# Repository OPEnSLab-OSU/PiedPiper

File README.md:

# PiedPiper
Click [here](https://github.com/OPEnSLab-OSU/OPEnS-Lab-Home/wiki/Pied-Piper) for the full Pied Piper Wiki

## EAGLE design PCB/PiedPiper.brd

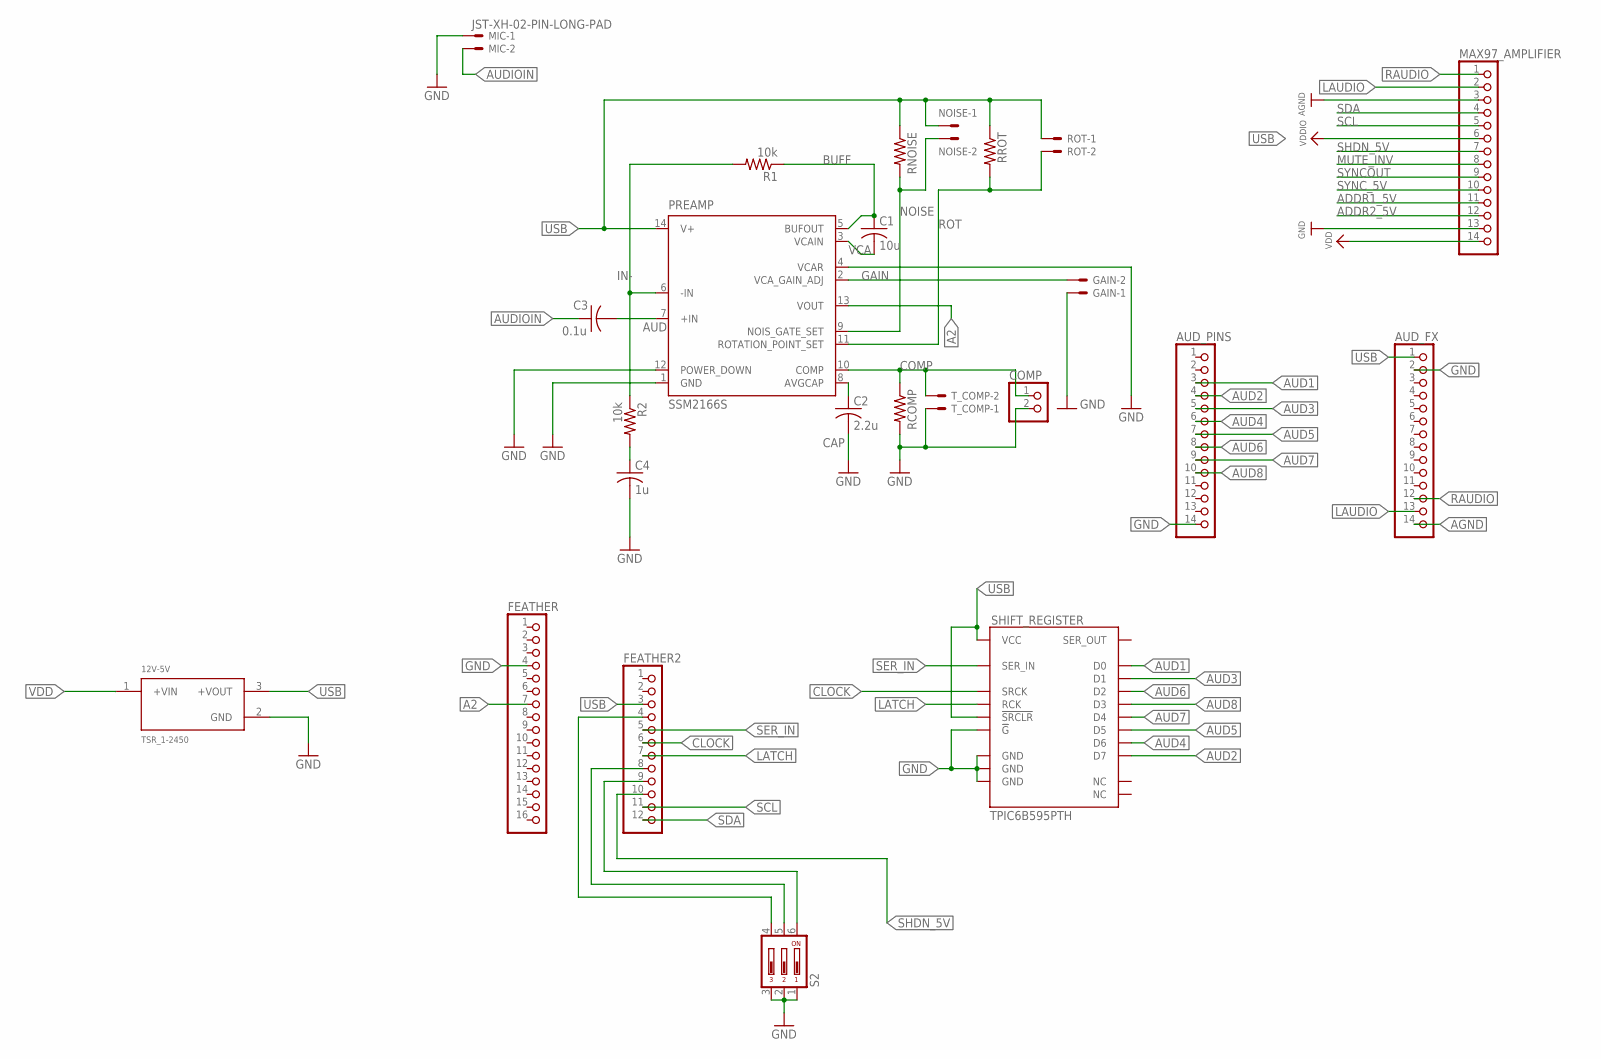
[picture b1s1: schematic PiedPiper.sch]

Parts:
12V-5V: TSR_1-2450; CONV_TSR_1-2450
AUD_FX: PINHD-1X14; 1X14
AUD_PINS: PINHD-1X14; 1X14
C1: 10u; C0805
C2: 2.2u; C0805
C3: 0.1u; C0805
C4: 1u; C0805
COMP: PINHD-1X2; 1X02
FEATHER: PINHD-1X16; 1X16
FEATHER2: PINHD-1X12; 1X12
GAIN: JST-XH-02-PIN-LONG-PAD; JST-XH-02-PACKAGE-LONG-PAD
MAX97_AMPLIFIER: HEADER-1X14; 1X14_ROUND70
MIC: JST-XH-02-PIN-LONG-PAD; JST-XH-02-PACKAGE-LONG-PAD
NOISE: JST-XH-02-PIN-LONG-PAD; JST-XH-02-PACKAGE-LONG-PAD
PREAMP: SSM2166S; SO14
R1, R2: 10k; R1206
RCOMP: R-US_R1206; R1206
RNOISE: R-US_R1206; R1206
ROT: JST-XH-02-PIN-LONG-PAD; JST-XH-02-PACKAGE-LONG-PAD
RROT: R-US_R1206; R1206
S2: DP03; DP-03
SHIFT_REGISTER: TPIC6B595PTH; DIL20
T_COMP: JST-XH-02-PIN-LONG-PAD; JST-XH-02-PACKAGE-LONG-PAD

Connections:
A2: FEATHER.7, PREAMP.13 (VOUT)
ADDR1_5V: MAX97_AMPLIFIER.11
ADDR2_5V: MAX97_AMPLIFIER.12
AGND: AUD_FX.14, MAX97_AMPLIFIER.3
AUD: C3.2, PREAMP.7 (+IN)
AUD1: AUD_PINS.3, SHIFT_REGISTER.4 (D0)
AUD2: AUD_PINS.4, SHIFT_REGISTER.17 (D7)
AUD3: AUD_PINS.5, SHIFT_REGISTER.5 (D1)
AUD4: AUD_PINS.6, SHIFT_REGISTER.16 (D6)
AUD5: AUD_PINS.7, SHIFT_REGISTER.15 (D5)
AUD6: AUD_PINS.8, SHIFT_REGISTER.6 (D2)
AUD7: AUD_PINS.9, SHIFT_REGISTER.14 (D4)
AUD8: AUD_PINS.10, SHIFT_REGISTER.7 (D3)
AUDIOIN: C3.1, MIC.2
BUFF: C1.1, PREAMP.5 (BUFOUT), R1.1
CAP: C2.1, PREAMP.8 (AVGCAP)
CLOCK: FEATHER2.6, SHIFT_REGISTER.13 (SRCK)
COMP: COMP.1, PREAMP.10 (COMP), RCOMP.1, T_COMP.2
GAIN: GAIN.2, PREAMP.2 (VCA_GAIN_ADJ)
GND: 12V-5V.2 (GND), AUD_FX.2, AUD_PINS.14, C2.2, C4.2, COMP.2, FEATHER.4, GAIN.1, MAX97_AMPLIFIER.13, MIC.1, PREAMP.1 (GND), PREAMP.4 (VCAR), PREAMP.12 (POWER_DOWN), RCOMP.2, S2.1, S2.2, S2.3, SHIFT_REGISTER.9 (!G), SHIFT_REGISTER.10 (GND), SHIFT_REGISTER.11 (GND), SHIFT_REGISTER.19 (GND), T_COMP.1
IN-: PREAMP.6 (-IN), R1.2, R2.1
LATCH: FEATHER2.7, SHIFT_REGISTER.12 (RCK)
LAUDIO: AUD_FX.13, MAX97_AMPLIFIER.2
MUTE_INV: MAX97_AMPLIFIER.8
unnamed: FEATHER2.8, S2.5
unnamed: FEATHER2.9, S2.6
unnamed: FEATHER2.4, S2.4
unnamed: C4.1, R2.2
NOISE: NOISE.2, PREAMP.9 (NOIS_GATE_SET), RNOISE.2
RAUDIO: AUD_FX.12, MAX97_AMPLIFIER.1
ROT: PREAMP.11 (ROTATION_POINT_SET), ROT.2, RROT.2
SCL: FEATHER2.11, MAX97_AMPLIFIER.5
SDA: FEATHER2.12, MAX97_AMPLIFIER.4
SER_IN: FEATHER2.5, SHIFT_REGISTER.3 (SER_IN)
SHDN_5V: FEATHER2.10, MAX97_AMPLIFIER.7
SYNCOUT: MAX97_AMPLIFIER.9
SYNC_5V: MAX97_AMPLIFIER.10
USB: 12V-5V.3 (+VOUT), AUD_FX.1, FEATHER2.3, MAX97_AMPLIFIER.6, NOISE.1, PREAMP.14 (V+), RNOISE.1, ROT.1, RROT.1, SHIFT_REGISTER.2 (VCC), SHIFT_REGISTER.8 (!SRCLR)
VCA: C1.2, PREAMP.3 (VCAIN)
VDD: 12V-5V.1 (+VIN), MAX97_AMPLIFIER.14

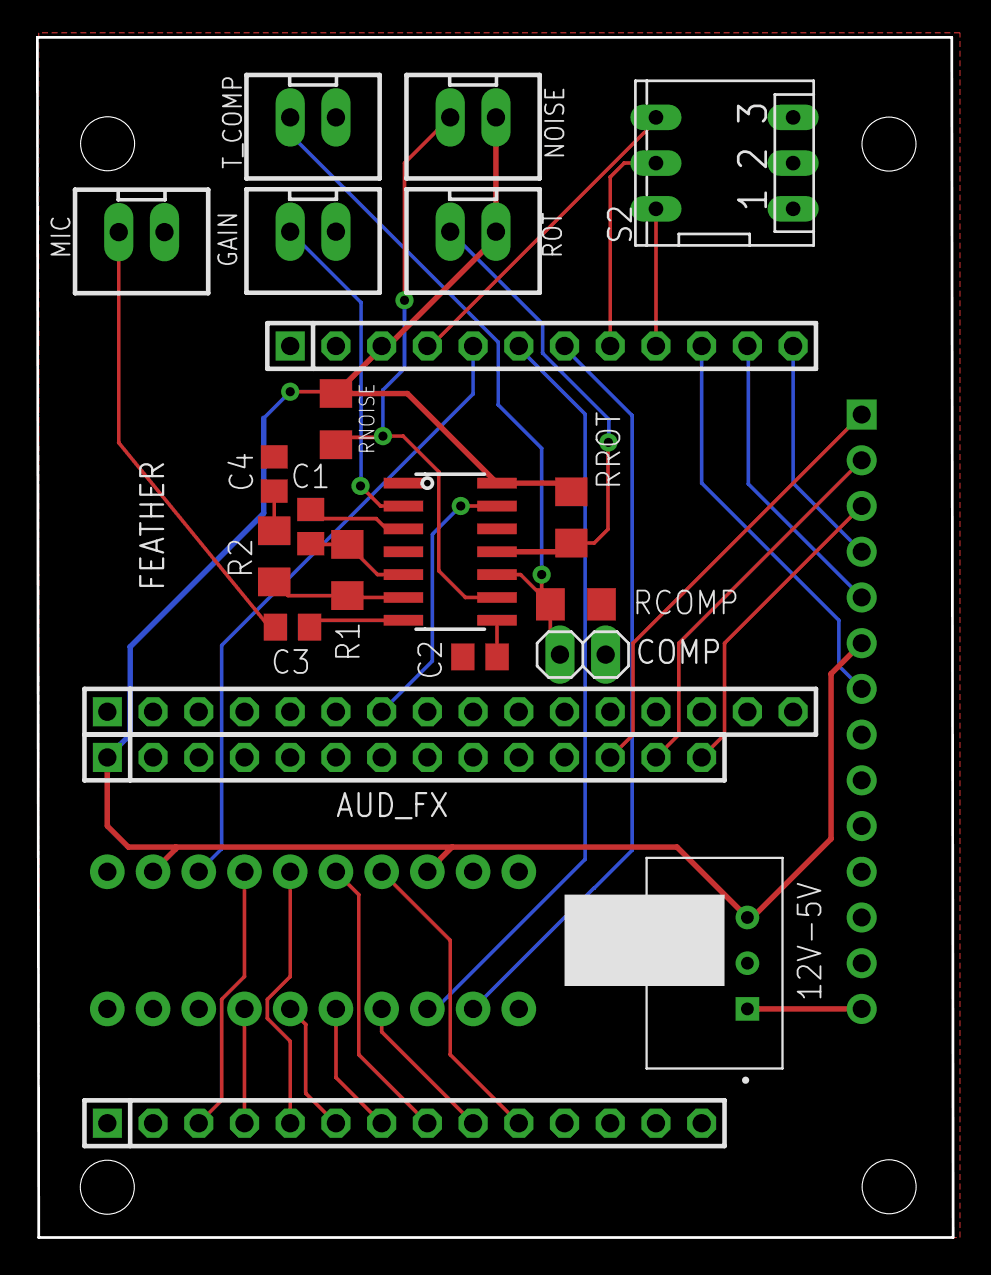
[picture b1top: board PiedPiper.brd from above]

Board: 2 copper layers, 50.9 x 66.7 mm, 24 parts (1 on the bottom side), 35 nets.

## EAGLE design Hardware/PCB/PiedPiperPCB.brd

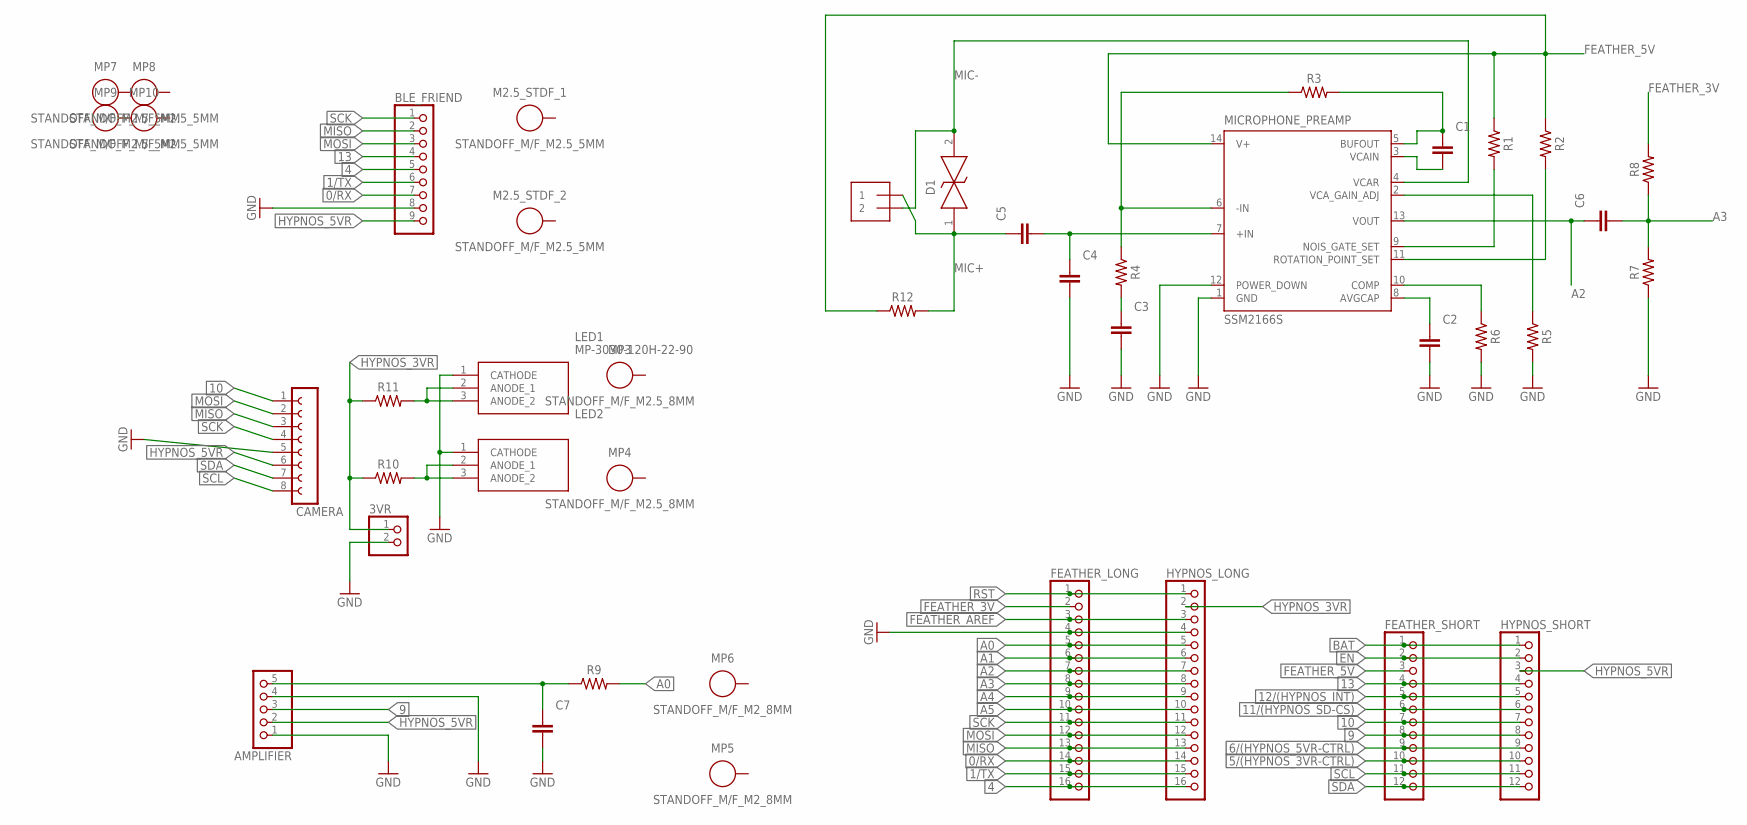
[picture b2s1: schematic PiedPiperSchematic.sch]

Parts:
3VR: PINHD-1X2; 1X02
AMPLIFIER: PINHD-1X05_2.54-S; 1X05-S
BLE_FRIEND: PINHD-1X09_2.54-S; 1X09-S
C1, C2, C3, C4, C5, C6, C7: C_CHIP-0805(2012-METRIC); CAPC2012X110
CAMERA: FE08W
D1: STS321033B100; SOD2613X100N
FEATHER_LONG: PINHD-1X16_2.54-S; 1X16-S
FEATHER_SHORT: PINHD-1X12_2.54-S; 1X12-S
HYPNOS_LONG: PINHD-1X16_2.54-S; 1X16-S
HYPNOS_SHORT: PINHD-1X12_2.54-S; 1X12-S
LED1, LED2: MP-3030-120H-22-90; MP3030120H2290
M2.5_STDF_1, M2.5_STDF_2: STANDOFF_M/F_M2.5_5MM; STANDOFF_HEX_MALE-FEMALE_500X500_M2.5X0.45_MTGP755H270
MICROPHONE_PREAMP: SSM2166S; SO14
MIC_INPT: 1X2-3.5MM
MP3, MP4: STANDOFF_M/F_M2.5_8MM; STANDOFF_HEX_MALE-FEMALE_500X800_M2.5X0.45_MTGP755H270
MP5, MP6: STANDOFF_M/F_M2_8MM; STANDOFF_HEX_MALE-FEMALE_400X800_M2X0.4_MTGP600H220
MP7, MP8, MP9, MP10: STANDOFF_M/F_M2.5_5MM; STANDOFF_HEX_MALE-FEMALE_500X500_M2.5X0.45_MTGP755H270
R1, R2, R3, R4, R5, R6, R7, R8, R9, R10, R11, R12: R-US_CHIP-1206(3216-METRIC); RESC3216X70

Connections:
0/RX: BLE_FRIEND.7, FEATHER_LONG.14, HYPNOS_LONG.14
1/TX: BLE_FRIEND.6, FEATHER_LONG.15, HYPNOS_LONG.15
4: BLE_FRIEND.5, FEATHER_LONG.16, HYPNOS_LONG.16
5/(HYPNOS_3VR-CTRL): FEATHER_SHORT.10, HYPNOS_SHORT.10
6/(HYPNOS_5VR-CTRL): FEATHER_SHORT.9, HYPNOS_SHORT.9
9: AMPLIFIER.3, FEATHER_SHORT.8, HYPNOS_SHORT.8
10: CAMERA.1, FEATHER_SHORT.7, HYPNOS_SHORT.7
11/(HYPNOS_SD-CS): FEATHER_SHORT.6, HYPNOS_SHORT.6
12/(HYPNOS_INT): FEATHER_SHORT.5, HYPNOS_SHORT.5
13: BLE_FRIEND.4, FEATHER_SHORT.4, HYPNOS_SHORT.4
A0: FEATHER_LONG.5, HYPNOS_LONG.5, R9.2
A1: FEATHER_LONG.6, HYPNOS_LONG.6
A2: C6.1, FEATHER_LONG.7, HYPNOS_LONG.7, MICROPHONE_PREAMP.13 (VOUT)
A3: C6.2, FEATHER_LONG.8, HYPNOS_LONG.8, R7.2, R8.1
A4: FEATHER_LONG.9, HYPNOS_LONG.9
A5: FEATHER_LONG.10, HYPNOS_LONG.10
AVGCAP: C2.1, MICROPHONE_PREAMP.8 (AVGCAP)
BAT: FEATHER_SHORT.1, HYPNOS_SHORT.1
BUFOUT: C1.1, MICROPHONE_PREAMP.5 (BUFOUT), R3.2
COMP: MICROPHONE_PREAMP.10 (COMP), R6.1
EN: FEATHER_SHORT.2, HYPNOS_SHORT.2
FEATHER_3V: FEATHER_LONG.2, R8.2
FEATHER_5V: FEATHER_SHORT.3, MICROPHONE_PREAMP.14 (V+), R1.1, R2.1, R12.1
FEATHER_AREF: FEATHER_LONG.3, HYPNOS_LONG.3
GND: 3VR.2, AMPLIFIER.1, AMPLIFIER.4, BLE_FRIEND.8, C2.2, C3.2, C4.2, C7.2, CAMERA.5, FEATHER_LONG.4, HYPNOS_LONG.4, LED1.1 (CATHODE), LED2.1 (CATHODE), MICROPHONE_PREAMP.1 (GND), MICROPHONE_PREAMP.12 (POWER_DOWN), R5.2, R6.2, R7.1
HYPNOS_3VR: 3VR.1, HYPNOS_LONG.2, R10.1, R11.1
HYPNOS_5VR: AMPLIFIER.2, BLE_FRIEND.9, CAMERA.6, HYPNOS_SHORT.3
IN+: C4.1, C5.2, MICROPHONE_PREAMP.7 (+IN)
IN-: MICROPHONE_PREAMP.6 (-IN), R3.1, R4.1
MIC+: C5.1, D1.1, MIC_INPT.1, R12.2
MIC-: D1.2, MICROPHONE_PREAMP.4 (VCAR), MIC_INPT.2
MISO: BLE_FRIEND.2, CAMERA.3, FEATHER_LONG.13, HYPNOS_LONG.13
MOSI: BLE_FRIEND.3, CAMERA.2, FEATHER_LONG.12, HYPNOS_LONG.12
unnamed: LED1.2 (ANODE_1), LED1.3 (ANODE_2), R11.2
unnamed: C3.1, R4.2
unnamed: AMPLIFIER.5, C7.1, R9.1
unnamed: LED2.2 (ANODE_1), LED2.3 (ANODE_2), R10.2
RGAIN: MICROPHONE_PREAMP.2 (VCA_GAIN_ADJ), R5.1
RNOISE: MICROPHONE_PREAMP.9 (NOIS_GATE_SET), R1.2
RROT: MICROPHONE_PREAMP.11 (ROTATION_POINT_SET), R2.2
RST: FEATHER_LONG.1, HYPNOS_LONG.1
SCK: BLE_FRIEND.1, CAMERA.4, FEATHER_LONG.11, HYPNOS_LONG.11
SCL: CAMERA.8, FEATHER_SHORT.11, HYPNOS_SHORT.11
SDA: CAMERA.7, FEATHER_SHORT.12, HYPNOS_SHORT.12
VCAIN: C1.2, MICROPHONE_PREAMP.3 (VCAIN)

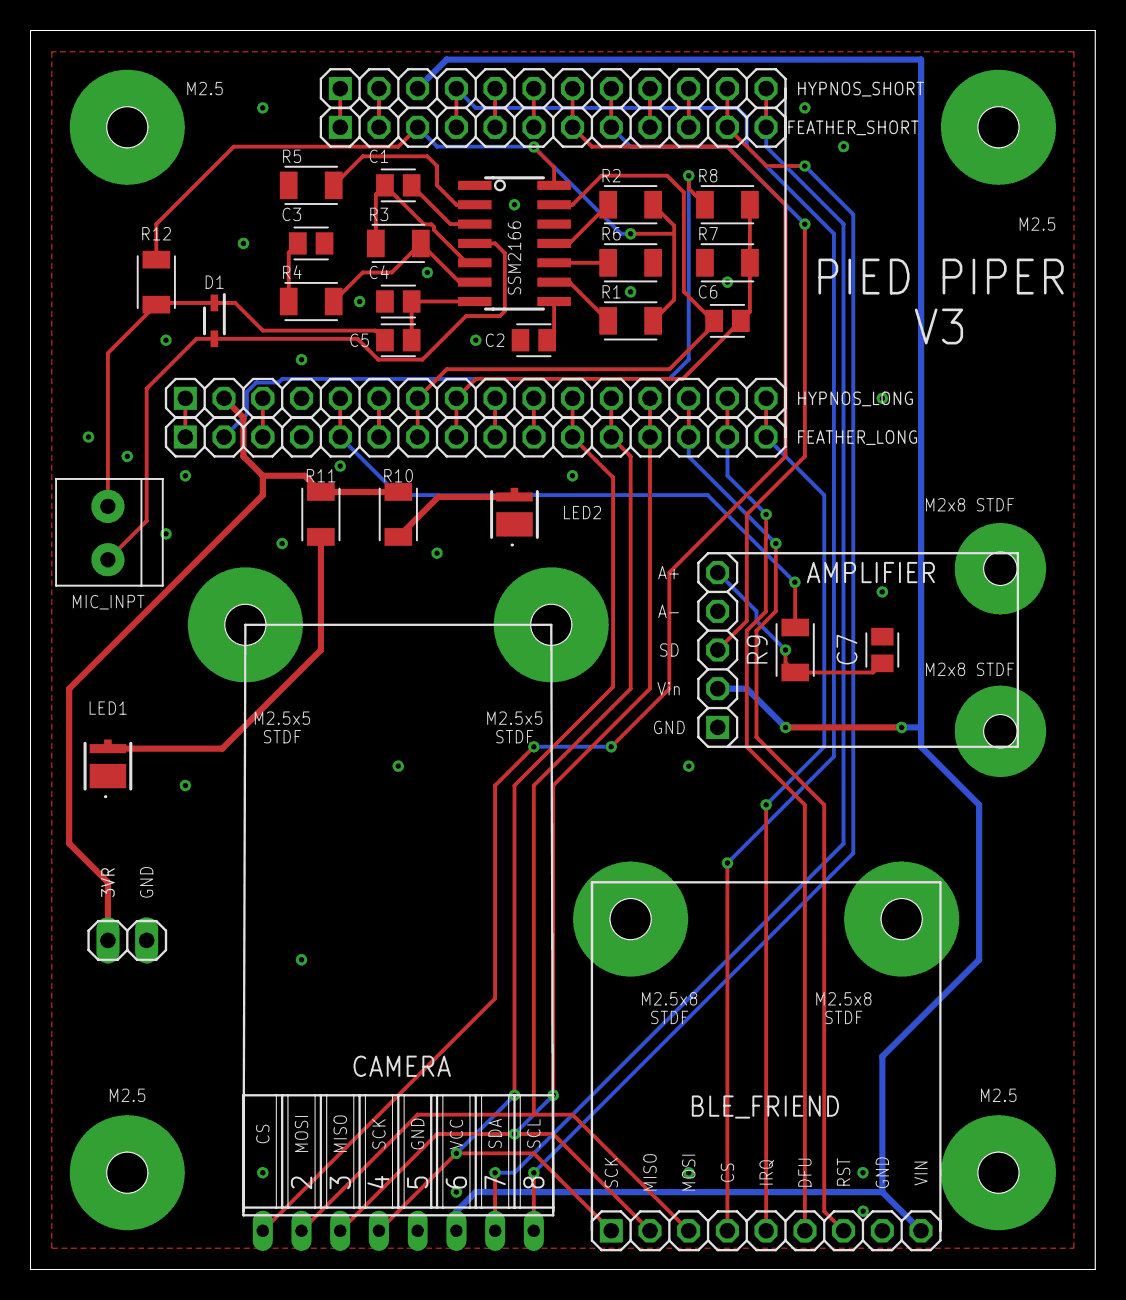
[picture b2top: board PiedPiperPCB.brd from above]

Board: 2 copper layers, 69.8 x 81.3 mm, 42 parts (0 on the bottom side), 45 nets.

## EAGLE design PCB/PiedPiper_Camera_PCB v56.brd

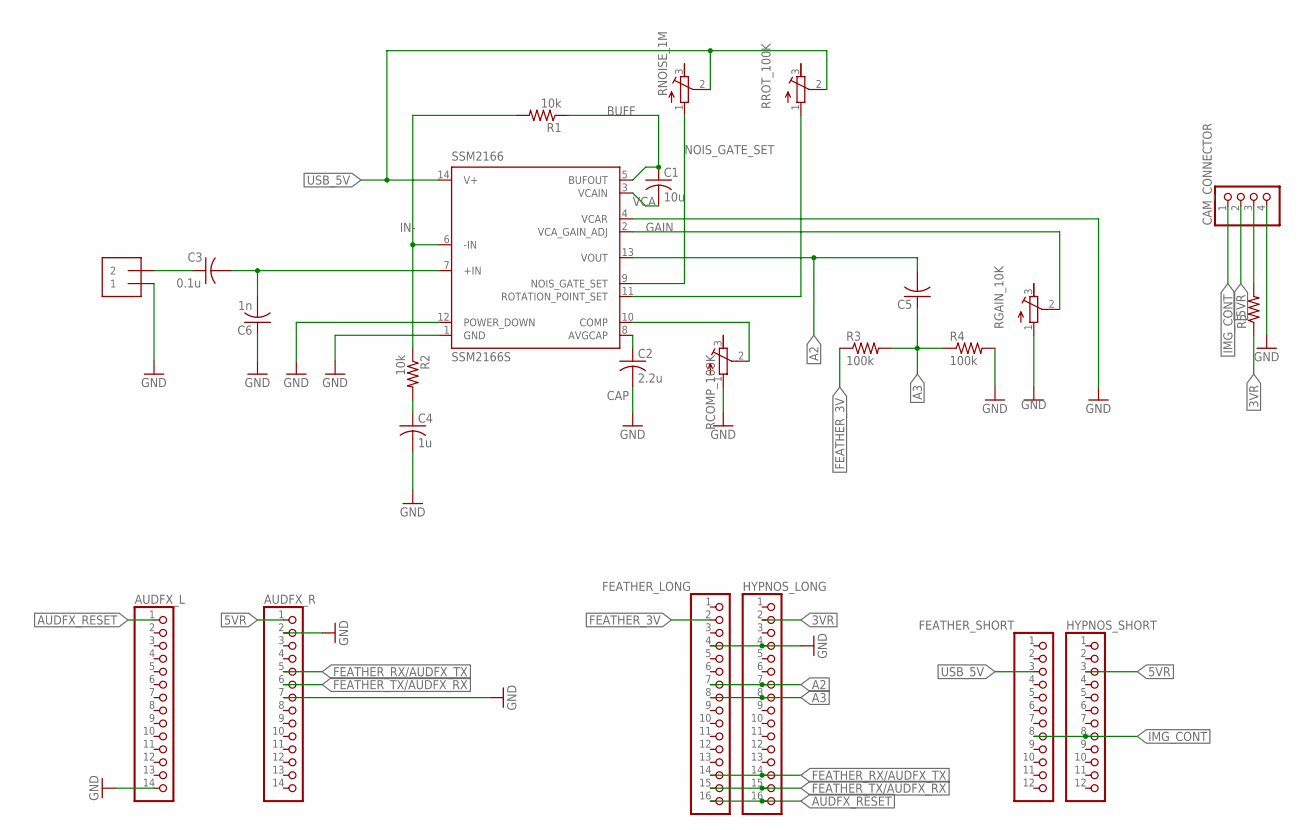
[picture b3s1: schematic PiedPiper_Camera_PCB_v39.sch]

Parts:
AUDFX_L: PINHD-1X14_2.54-S; 1X14-S
AUDFX_R: PINHD-1X14_2.54-S; 1X14-S
AUDIO_IN: 1X2-3.5MM
C1: 10u; C0805
C2: 2.2u; C0805
C3: 0.1u; C0805
C4: 1u; C0805
C5: C-USC0805; C0805
C6: 1n; C0805
CAM_CONNECTOR: PINHD-1X4; 1X04
FEATHER_LONG: PINHD-1X16_2.54-S; 1X16-S
FEATHER_SHORT: PINHD-1X12_2.54-S; 1X12-S
HYPNOS_LONG: PINHD-1X16_2.54-S; 1X16-S
HYPNOS_SHORT: PINHD-1X12_2.54-S; 1X12-S
R1, R2: 10k; R1206
R3, R4: 100k; R1206
R5: R-US_R1206; R1206
RCOMP_100K: R-TRIMM3296Y; RTRIM3296Y
RGAIN_10K: R-TRIMM3296Y; RTRIM3296Y
RNOISE_1M: R-TRIMM3296Y; RTRIM3296Y
RROT_100K: R-TRIMM3296Y; RTRIM3296Y
SSM2166: SSM2166S; SO14

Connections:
3VR: HYPNOS_LONG.2, R5.1
5VR: AUDFX_R.1, CAM_CONNECTOR.2, HYPNOS_SHORT.3
+IN: C3.2, C6.2, SSM2166.7 (+IN)
A2: C5.2, FEATHER_LONG.7, HYPNOS_LONG.7, SSM2166.13 (VOUT)
A3: C5.1, FEATHER_LONG.8, HYPNOS_LONG.8, R3.2, R4.1
AUDFX_RESET: AUDFX_L.1, FEATHER_LONG.16, HYPNOS_LONG.16
BUFF: C1.1, R1.1, SSM2166.5 (BUFOUT)
CAP: C2.1, SSM2166.8 (AVGCAP)
COMP: RCOMP_100K.2 (S), SSM2166.10 (COMP)
FEATHER_3V: FEATHER_LONG.2, R3.1
FEATHER_RX/AUDFX_TX: AUDFX_R.5, FEATHER_LONG.14, HYPNOS_LONG.14
FEATHER_TX/AUDFX_RX: AUDFX_R.6, FEATHER_LONG.15, HYPNOS_LONG.15
GAIN: RGAIN_10K.2 (S), SSM2166.2 (VCA_GAIN_ADJ)
GND: AUDFX_L.14, AUDFX_R.2, AUDFX_R.7, AUDIO_IN.1, C2.2, C4.2, C6.1, CAM_CONNECTOR.4, FEATHER_LONG.4, HYPNOS_LONG.4, R4.2, RCOMP_100K.1 (A), RGAIN_10K.1 (A), SSM2166.1 (GND), SSM2166.4 (VCAR), SSM2166.12 (POWER_DOWN)
IMG_CONT: CAM_CONNECTOR.1, FEATHER_SHORT.8, HYPNOS_SHORT.8
IN-: R1.2, R2.1, SSM2166.6 (-IN)
unnamed: CAM_CONNECTOR.3, R5.2
unnamed: AUDIO_IN.2, C3.1
unnamed: C4.1, R2.2
NOIS_GATE_SET: RNOISE_1M.1 (A), SSM2166.9 (NOIS_GATE_SET)
ROTATION_POINT_SET: RROT_100K.1 (A), SSM2166.11 (ROTATION_POINT_SET)
USB_5V: FEATHER_SHORT.3, RNOISE_1M.2 (S), RROT_100K.2 (S), SSM2166.14 (V+)
VCA: C1.2, SSM2166.3 (VCAIN)

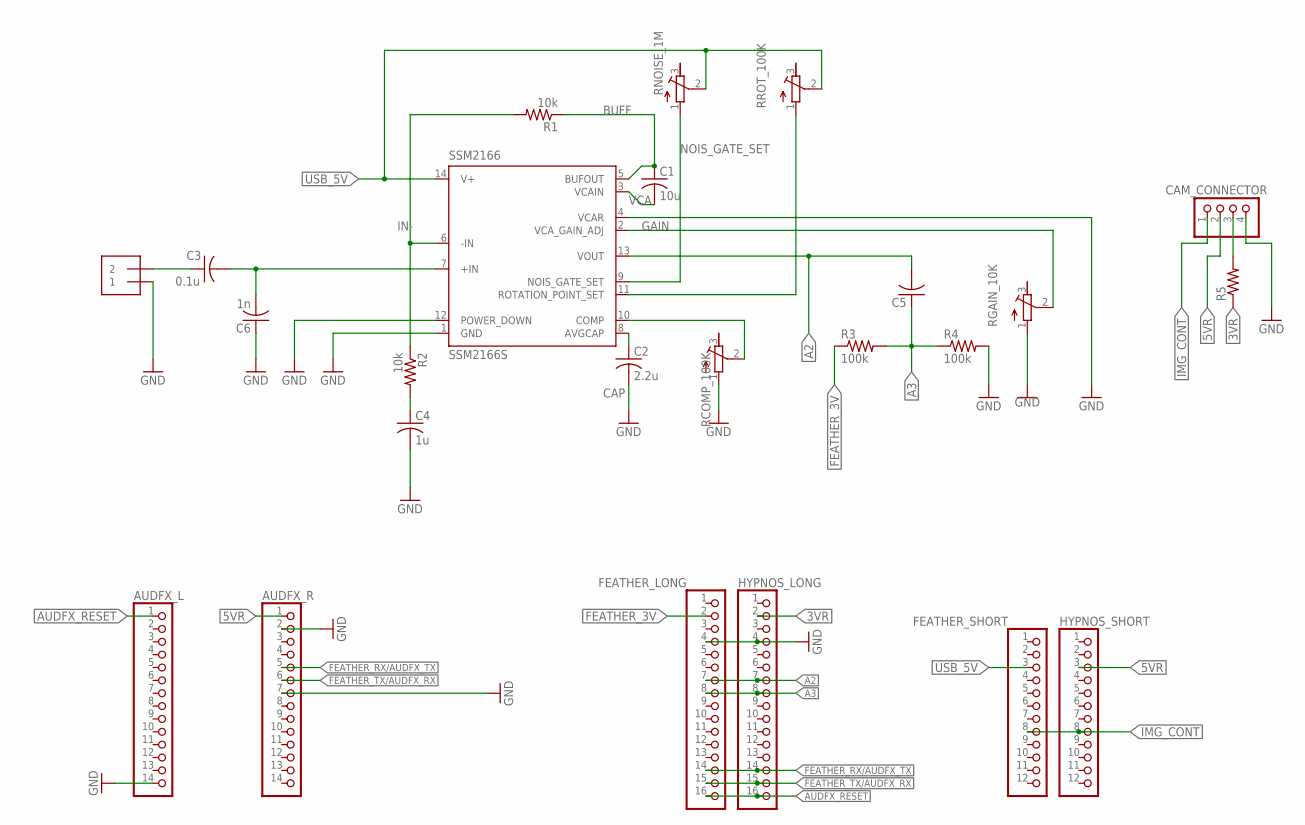
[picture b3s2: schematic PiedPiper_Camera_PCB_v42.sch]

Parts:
AUDFX_L: PINHD-1X14_2.54-S; 1X14-S
AUDFX_R: PINHD-1X14_2.54-S; 1X14-S
AUDIO_IN: 1X2-3.5MM
C1: 10u; C0805
C2: 2.2u; C0805
C3: 0.1u; C0805
C4: 1u; C0805
C5: C-USC0805; C0805
C6: 1n; C0805
CAM_CONNECTOR: PINHD-1X4; 1X04
FEATHER_LONG: PINHD-1X16_2.54-S; 1X16-S
FEATHER_SHORT: PINHD-1X12_2.54-S; 1X12-S
HYPNOS_LONG: PINHD-1X16_2.54-S; 1X16-S
HYPNOS_SHORT: PINHD-1X12_2.54-S; 1X12-S
R1, R2: 10k; R1206
R3, R4: 100k; R1206
R5: R-US_R1206; R1206
RCOMP_100K: R-TRIMM3296Y; RTRIM3296Y
RGAIN_10K: R-TRIMM3296Y; RTRIM3296Y
RNOISE_1M: R-TRIMM3296Y; RTRIM3296Y
RROT_100K: R-TRIMM3296Y; RTRIM3296Y
SSM2166: SSM2166S; SO14

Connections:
3VR: HYPNOS_LONG.2, R5.1
5VR: AUDFX_R.1, CAM_CONNECTOR.2, HYPNOS_SHORT.3
+IN: C3.2, C6.2, SSM2166.7 (+IN)
A2: C5.2, FEATHER_LONG.7, HYPNOS_LONG.7, SSM2166.13 (VOUT)
A3: C5.1, FEATHER_LONG.8, HYPNOS_LONG.8, R3.2, R4.1
AUDFX_RESET: AUDFX_L.1, FEATHER_LONG.16, HYPNOS_LONG.16
BUFF: C1.1, R1.1, SSM2166.5 (BUFOUT)
CAP: C2.1, SSM2166.8 (AVGCAP)
COMP: RCOMP_100K.2 (S), SSM2166.10 (COMP)
FEATHER_3V: FEATHER_LONG.2, R3.1
FEATHER_RX/AUDFX_TX: AUDFX_R.5, FEATHER_LONG.14, HYPNOS_LONG.14
FEATHER_TX/AUDFX_RX: AUDFX_R.6, FEATHER_LONG.15, HYPNOS_LONG.15
GAIN: RGAIN_10K.2 (S), SSM2166.2 (VCA_GAIN_ADJ)
GND: AUDFX_L.14, AUDFX_R.2, AUDFX_R.7, AUDIO_IN.1, C2.2, C4.2, C6.1, CAM_CONNECTOR.4, FEATHER_LONG.4, HYPNOS_LONG.4, R4.2, RCOMP_100K.1 (A), RGAIN_10K.1 (A), SSM2166.1 (GND), SSM2166.4 (VCAR), SSM2166.12 (POWER_DOWN)
IMG_CONT: CAM_CONNECTOR.1, FEATHER_SHORT.8, HYPNOS_SHORT.8
IN-: R1.2, R2.1, SSM2166.6 (-IN)
unnamed: CAM_CONNECTOR.3, R5.2
unnamed: AUDIO_IN.2, C3.1
unnamed: C4.1, R2.2
NOIS_GATE_SET: RNOISE_1M.1 (A), SSM2166.9 (NOIS_GATE_SET)
ROTATION_POINT_SET: RROT_100K.1 (A), SSM2166.11 (ROTATION_POINT_SET)
USB_5V: FEATHER_SHORT.3, RNOISE_1M.2 (S), RROT_100K.2 (S), SSM2166.14 (V+)
VCA: C1.2, SSM2166.3 (VCAIN)

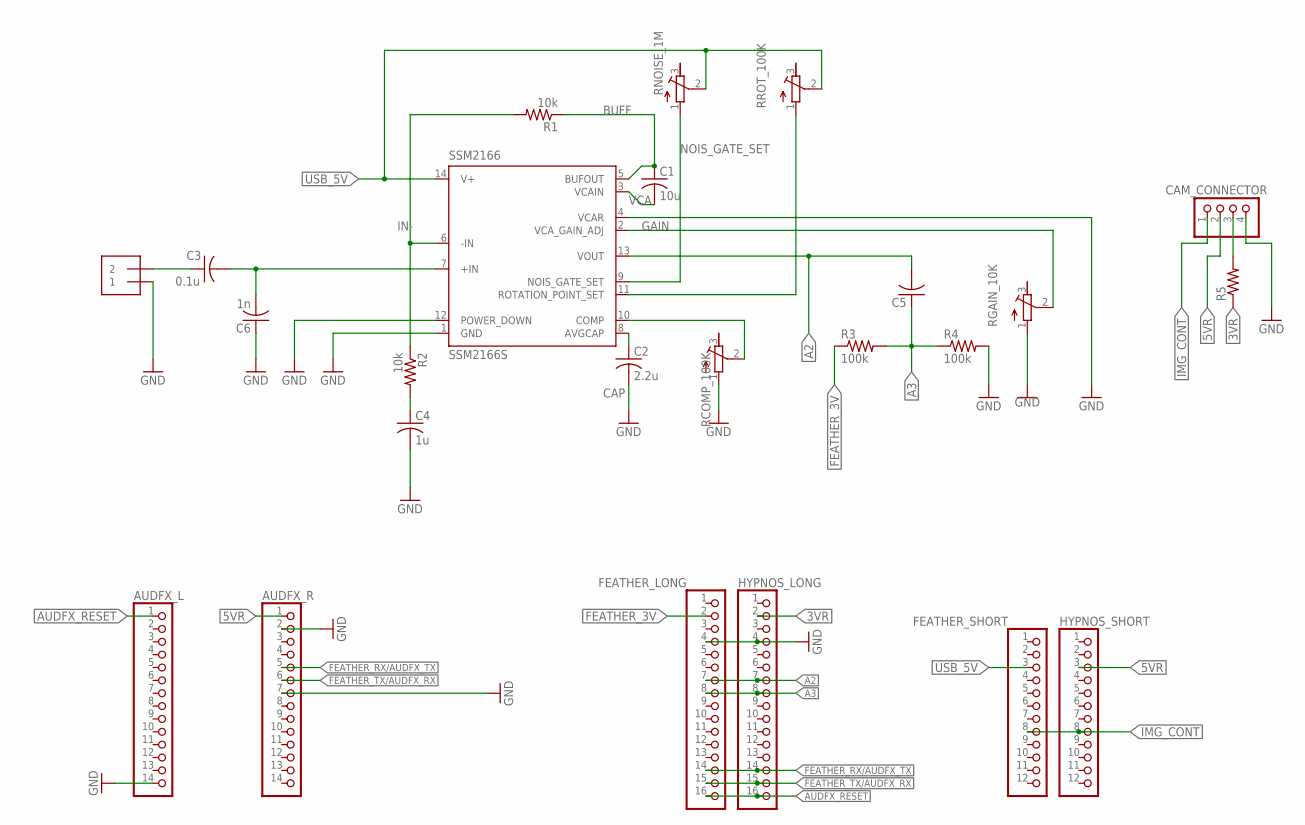
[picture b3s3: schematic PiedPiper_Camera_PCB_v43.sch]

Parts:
AUDFX_L: PINHD-1X14_2.54-S; 1X14-S
AUDFX_R: PINHD-1X14_2.54-S; 1X14-S
AUDIO_IN: 1X2-3.5MM
C1: 10u; C0805
C2: 2.2u; C0805
C3: 0.1u; C0805
C4: 1u; C0805
C5: C-USC0805; C0805
C6: 1n; C0805
CAM_CONNECTOR: PINHD-1X4; 1X04
FEATHER_LONG: PINHD-1X16_2.54-S; 1X16-S
FEATHER_SHORT: PINHD-1X12_2.54-S; 1X12-S
HYPNOS_LONG: PINHD-1X16_2.54-S; 1X16-S
HYPNOS_SHORT: PINHD-1X12_2.54-S; 1X12-S
R1, R2: 10k; R1206
R3, R4: 100k; R1206
R5: R-US_R1206; R1206
RCOMP_100K: R-TRIMM3296Y; RTRIM3296Y
RGAIN_10K: R-TRIMM3296Y; RTRIM3296Y
RNOISE_1M: R-TRIMM3296Y; RTRIM3296Y
RROT_100K: R-TRIMM3296Y; RTRIM3296Y
SSM2166: SSM2166S; SO14

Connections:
3VR: HYPNOS_LONG.2, R5.1
5VR: AUDFX_R.1, CAM_CONNECTOR.2, HYPNOS_SHORT.3
+IN: C3.2, C6.2, SSM2166.7 (+IN)
A2: C5.2, FEATHER_LONG.7, HYPNOS_LONG.7, SSM2166.13 (VOUT)
A3: C5.1, FEATHER_LONG.8, HYPNOS_LONG.8, R3.2, R4.1
AUDFX_RESET: AUDFX_L.1, FEATHER_LONG.16, HYPNOS_LONG.16
BUFF: C1.1, R1.1, SSM2166.5 (BUFOUT)
CAP: C2.1, SSM2166.8 (AVGCAP)
COMP: RCOMP_100K.2 (S), SSM2166.10 (COMP)
FEATHER_3V: FEATHER_LONG.2, R3.1
FEATHER_RX/AUDFX_TX: AUDFX_R.5, FEATHER_LONG.14, HYPNOS_LONG.14
FEATHER_TX/AUDFX_RX: AUDFX_R.6, FEATHER_LONG.15, HYPNOS_LONG.15
GAIN: RGAIN_10K.2 (S), SSM2166.2 (VCA_GAIN_ADJ)
GND: AUDFX_L.14, AUDFX_R.2, AUDFX_R.7, AUDIO_IN.1, C2.2, C4.2, C6.1, CAM_CONNECTOR.4, FEATHER_LONG.4, HYPNOS_LONG.4, R4.2, RCOMP_100K.1 (A), RGAIN_10K.1 (A), SSM2166.1 (GND), SSM2166.4 (VCAR), SSM2166.12 (POWER_DOWN)
IMG_CONT: CAM_CONNECTOR.1, FEATHER_SHORT.8, HYPNOS_SHORT.8
IN-: R1.2, R2.1, SSM2166.6 (-IN)
unnamed: CAM_CONNECTOR.3, R5.2
unnamed: AUDIO_IN.2, C3.1
unnamed: C4.1, R2.2
NOIS_GATE_SET: RNOISE_1M.1 (A), SSM2166.9 (NOIS_GATE_SET)
ROTATION_POINT_SET: RROT_100K.1 (A), SSM2166.11 (ROTATION_POINT_SET)
USB_5V: FEATHER_SHORT.3, RNOISE_1M.2 (S), RROT_100K.2 (S), SSM2166.14 (V+)
VCA: C1.2, SSM2166.3 (VCAIN)

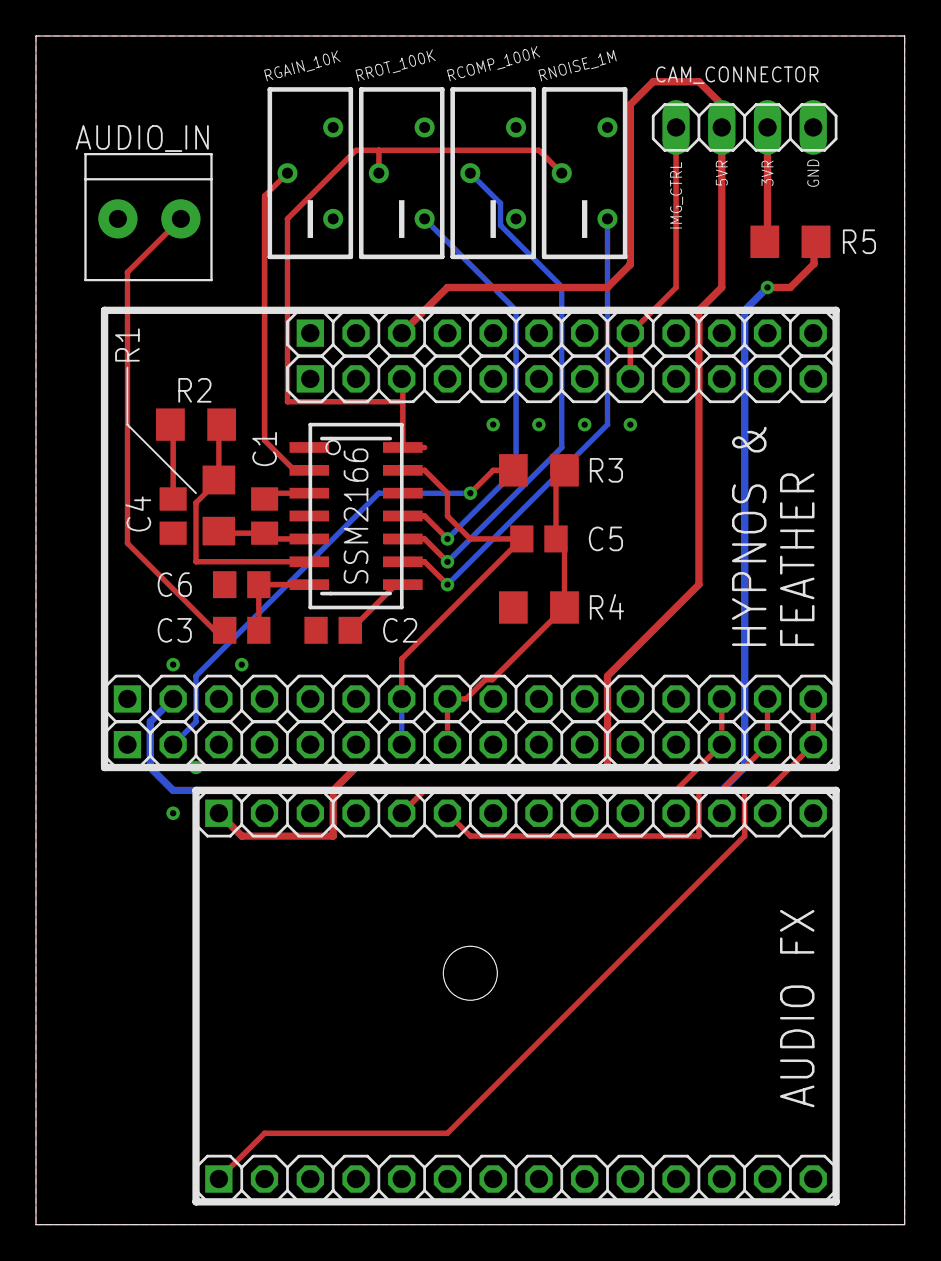
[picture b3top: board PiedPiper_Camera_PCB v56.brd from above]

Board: 2 copper layers, 48.3 x 66.0 mm, 24 parts (0 on the bottom side), 23 nets.

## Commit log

2019-11-12 Create foo
2019-11-12 Added Pied Piper 3D Models
2019-11-12 Added Pied Piper PCB Board
2019-11-12 Added Pied Piper Schematic
2019-11-22 Added Contact Mic 3D model
2019-11-22 Rename piedPiperMain.ino to Code/piedPiperMain.ino
2019-11-22 Updated playback
2020-01-27 Fixed a bug in detection algorithm
2020-04-30 Changed contact mic design
    New design gives the contact mic a stronger hold and uses less filament when printing
2020-06-15 Updated Pied Piper Trap STL files
2020-07-27 Added DEBUG mode
2020-07-27 Added hotswap DEBUG mode
2020-07-27 Fixed RTC/SD issue, added operation modes
    Adopted code to new PCB with shutdown for MAX9477 amplifier, added different operational modes(Full,No Playback, Gain Calibration, Audio Playback)
2020-08-25 Added 2 additional run modes
2020-08-28 Added function headers and improved comments
2020-09-14 Added code to parse recorded audio from Pied Piper
2020-09-14 Added automated grapher
    Generates waveforms of the data recorded from the piedPiper generated from the piedPiperAudioParser code
2020-09-14 updated code name
2020-10-19 Adjusting detection algorithm
2020-11-05 Added updated PCB
2020-11-09 Create STL
2020-11-10 Moved STL into folder
2021-01-21 Added noise generation software
2021-02-10 Added spectrogram tool
    Added a live spectrogram tool that can be used to stream processed audio off of the unit. A new operating mode was added (100) to use it.
2021-07-23 Camera
    Added software support for the camera
2021-07-23 Added camera support
    The camera used pin 10 for power control and pin 7 for imaging control
2021-08-06 Updated to reflect new hardware changes
    Camera power and imaging control pins have been remapped.
2021-08-09 Added status report log
    It's now easier to tell when problems occur (if any), because the system will periodically record whether or not it is alive, to the text file "Log.txt"
2021-08-15 Added serial debugging tools
2021-08-16 Reorganization
    Reorganized files and added .zenodo.json for publishing to Zenodo.
2021-08-16 Fixed json
    i missed a comma last time whoops
2021-08-18 Detection algorithm improved
    The detection algorithm is now less likely to output a false positive in response to intense transient noise.
2021-08-26 Updated PCB
2021-08-26 Added preview materials
    PDF and PNG files of the schematic and PCB have been added.
2021-08-26 Reorganized files
2021-08-26 Added CAM output zip
2021-08-27 Revised PCB
    Removed unnecessary ground traces, slightly reduced lengths of 5VR and 3VR traces, and added wire labels to camera connector pads.
2021-08-27 Another PCB revision
    Uploaded new PCB revision (in collaboration with Bryson) which includes ground plane vias to reduce capacitance.
2021-09-06 Added camera housing CAD files; fixed bug
2021-09-07 Fixed filenames
2021-09-07 Reorganized files and added sample printing utility
2021-09-07 Updated CAD files
2021-09-07 Adjusted detection algorithm frequency margin
2021-09-08 Fixed bug
    Added correct hypnos pin configuration to waveform viewer utility
2021-09-08 Added pre-arranged parts file for 3D printing.
2021-09-08 Added correct playback number for Hypnos
2021-09-09 SD always on
2021-09-11 Updated arranged parts file
2021-09-19 Fixed takePhoto
    Pin configuration commands were mistakenly commented out
2021-11-05 Uploaded parser to repo
    The parser used for generating spectrograms and audio files from raw detection data has been uploaded.
2021-11-05 Refactored code
2021-11-11 Improved code documentation
2021-12-27 Minor refactoring
2022-05-09 Fixed typo
2022-05-09 Removed files that were deleted from camera branch
2022-05-09 Added new PCB files
2022-05-09 Added labels to 3VR pads
2022-05-09 Fixed schematic and PCB version issue
2022-05-12 Updated CAM files
2022-06-15 Added support for new playback hardware
2022-07-18 Updated detection algorithm parameters
2023-02-02 Reformatting & documentation
2023-06-27 Added ArduinoFFTFloat dependency
2023-07-07 Reorganized files & added some utilities
2023-08-28 adding dependencies folder along with minor changes to software
2023-09-19 downsampling implementation v1
2023-10-07 resampling implemented
2023-10-10 resampling fixes
2023-10-18 resampling bug fixes, optimizations
2023-10-30 bug fixes
2024-03-05 Minor refactoring
    Changed significance threshold value to something that won't change depending on the FFT size.
2024-03-12 Updated CAD Files
    Updated CAD Files
2024-09-09 Added dependencies, mating call data
    Added software dependencies for PiedPiper.ino and included Tortistilus albidosparsus mating calls recorded by Rachele Nieri
2024-09-11 Updated filename

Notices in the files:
parts and their libraries:
microbuilder: This work is placed in the public domain, and may be freely used for commercial and non-commercial work with the following conditions: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
